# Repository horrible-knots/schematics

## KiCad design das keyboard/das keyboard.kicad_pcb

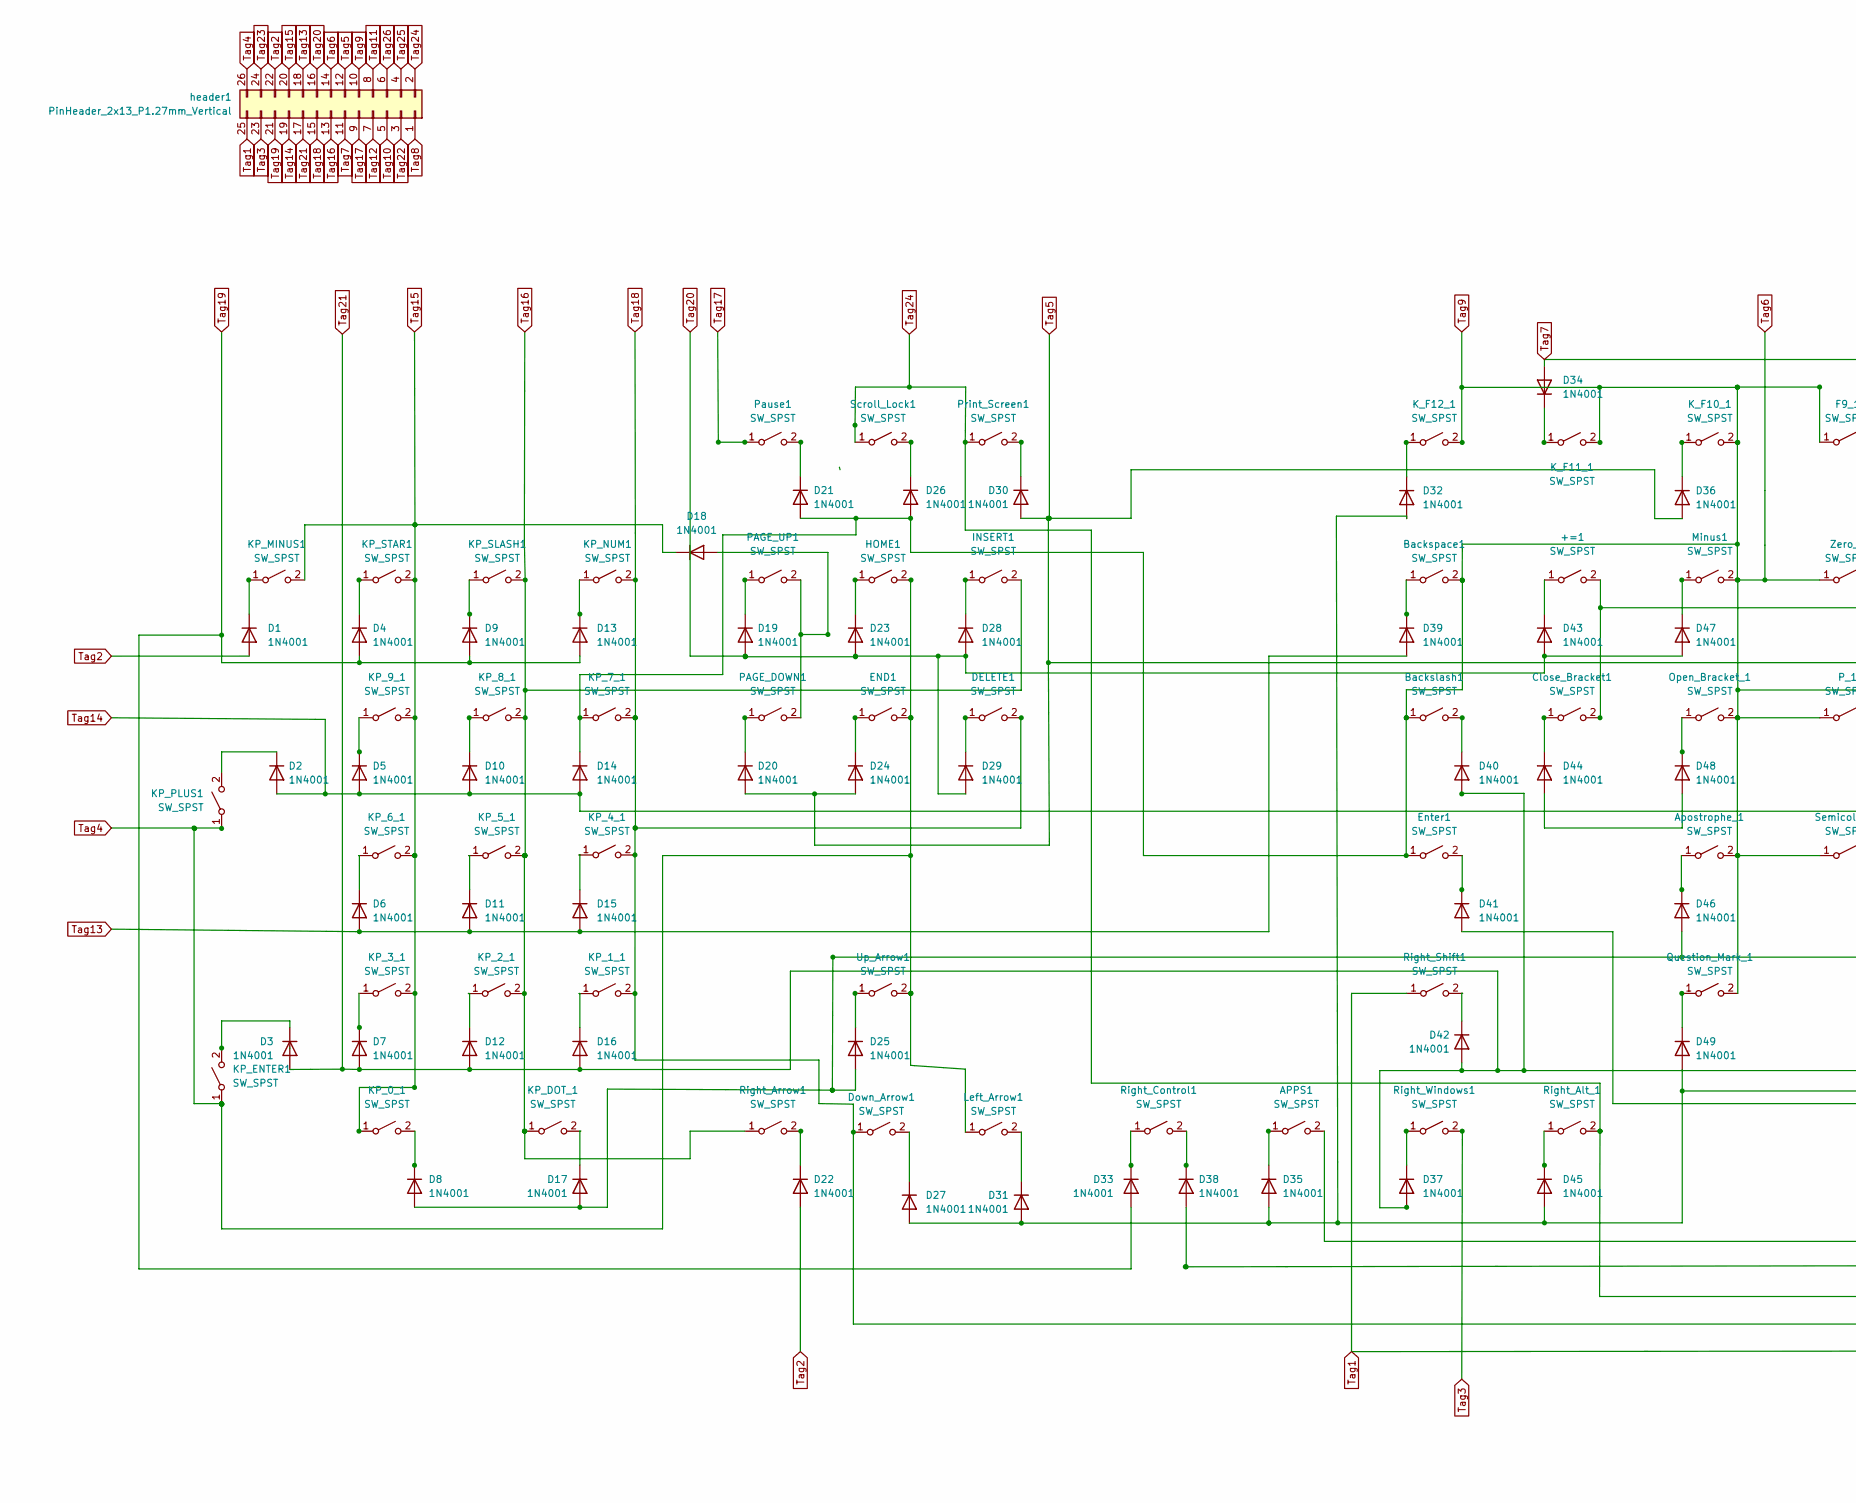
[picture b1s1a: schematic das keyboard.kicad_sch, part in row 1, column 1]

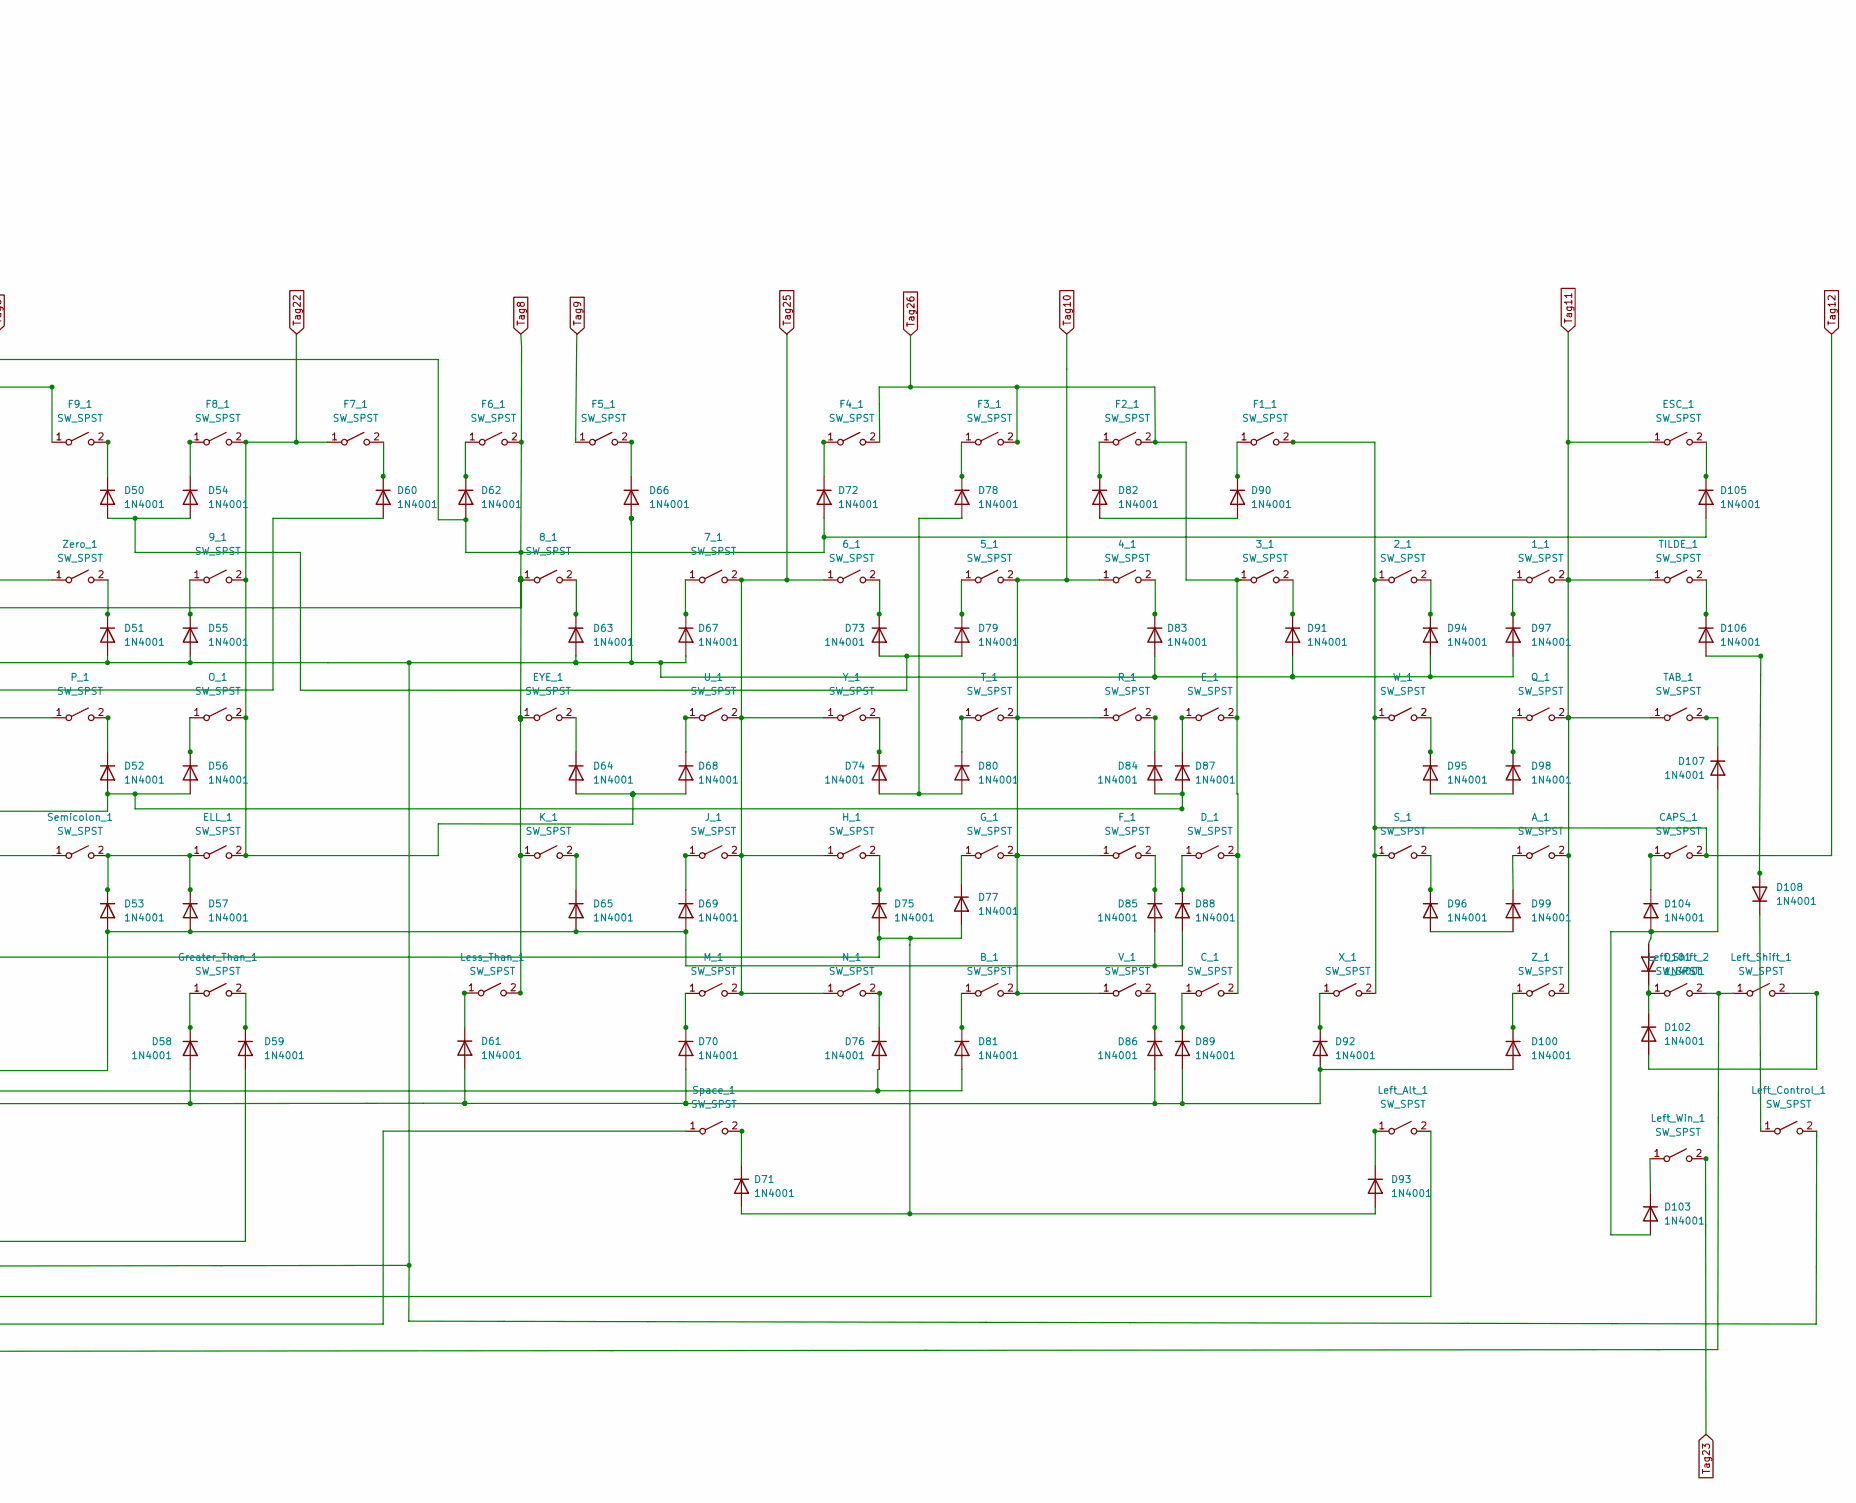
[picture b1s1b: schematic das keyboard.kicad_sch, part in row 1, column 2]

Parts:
1_1, 2_1, 3_1, 4_1, 5_1, 6_1, 7_1, 8_1, 9_1: SW_SPST; SW_Cherry_MX_1.00u_PCB
+=1: SW_SPST; SW_Cherry_MX_1.00u_PCB
APPS1: SW_SPST; SW_Cherry_MX_1.00u_PCB
A_1: SW_SPST; SW_Cherry_MX_1.00u_PCB
Apostrophe_1: SW_SPST; SW_Cherry_MX_1.00u_PCB
B_1: SW_SPST; SW_Cherry_MX_1.00u_PCB
Backslash1: SW_SPST; SW_Cherry_MX_1.50u_PCB
Backspace1: SW_SPST; SW_Cherry_MX_2.00u_PCB
CAPS_1: SW_SPST; SW_Cherry_MX_1.50u_PCB
C_1: SW_SPST; SW_Cherry_MX_1.00u_PCB
Close_Bracket1: SW_SPST; SW_Cherry_MX_1.00u_PCB
D1, D2, D3, D4, D5, D6, D7, D8, D9, D10, D11, D12, D13, D14, D15, D16, D17, D18, D19, D20, D21, D22, D23, D24, D25, D26, D27, D28, D29, D30, D31, D32, D33, D34, D35, D36, D37, D38, D39, D40, D41, D42, D43, D44, D45, D46, D47, D48, D49, D50, D51, D52, D53, D54, D55, D56, D57, D58, D59, D60, D61, D62, D63, D64, D65, D66, D67, D68, D69, D70, D71, D72, D73, D74, D75, D76, D77, D78, D79, D80, D81, D82, D83, D84, D85, D86, D87, D88, D89, D90, D91, D92, D93, D94, D95, D96, D97, D98, D99, D100, D101, D102, D103, D104, D105, D106, D107, D108: 1N4001; D_DO-41_SOD81_P10.16mm_Horizontal
DELETE1: SW_SPST; SW_Cherry_MX_1.00u_PCB
D_1: SW_SPST; SW_Cherry_MX_1.00u_PCB
Down_Arrow1: SW_SPST; SW_Cherry_MX_1.00u_PCB
ELL_1: SW_SPST; SW_Cherry_MX_1.00u_PCB
END1: SW_SPST; SW_Cherry_MX_1.00u_PCB
ESC_1: SW_SPST; SW_Cherry_MX_1.00u_PCB
EYE_1: SW_SPST; SW_Cherry_MX_1.00u_PCB
E_1: SW_SPST; SW_Cherry_MX_1.00u_PCB
Enter1: SW_SPST; SW_Cherry_MX_2.00u_PCB
F1_1, F2_1, F3_1, F4_1, F5_1, F6_1, F7_1, F8_1, F9_1: SW_SPST; SW_Cherry_MX_1.00u_PCB
F_1: SW_SPST; SW_Cherry_MX_1.00u_PCB
G_1: SW_SPST; SW_Cherry_MX_1.00u_PCB
Greater_Than_1: SW_SPST; SW_Cherry_MX_1.00u_PCB
HOME1: SW_SPST; SW_Cherry_MX_1.00u_PCB
H_1: SW_SPST; SW_Cherry_MX_1.00u_PCB
INSERT1: SW_SPST; SW_Cherry_MX_1.00u_PCB
J_1: SW_SPST; SW_Cherry_MX_1.00u_PCB
KP_0_1: SW_SPST; SW_Cherry_MX_2.00u_PCB
KP_1_1, KP_2_1, KP_3_1, KP_4_1, KP_5_1, KP_6_1, KP_7_1, KP_8_1, KP_9_1: SW_SPST; SW_Cherry_MX_1.00u_PCB
KP_DOT_1: SW_SPST; SW_Cherry_MX_1.00u_PCB
KP_ENTER1: SW_SPST; SW_Cherry_MX_2.00u_PCB
KP_MINUS1: SW_SPST; SW_Cherry_MX_1.00u_PCB
KP_NUM1: SW_SPST; SW_Cherry_MX_1.00u_PCB
KP_PLUS1: SW_SPST; SW_Cherry_MX_2.00u_PCB
KP_SLASH1: SW_SPST; SW_Cherry_MX_1.00u_PCB
KP_STAR1: SW_SPST; SW_Cherry_MX_1.00u_PCB
K_1: SW_SPST; SW_Cherry_MX_1.00u_PCB
K_F10_1, K_F11_1, K_F12_1: SW_SPST; SW_Cherry_MX_1.00u_PCB
Left_Alt_1: SW_SPST; SW_Cherry_MX_1.25u_PCB
Left_Arrow1: SW_SPST; SW_Cherry_MX_1.00u_PCB
Left_Control_1: SW_SPST; SW_Cherry_MX_1.25u_PCB
Left_Shift_1, Left_Shift_2: SW_SPST; SW_Cherry_MX_2.00u_PCB
Left_Win_1: SW_SPST; SW_Cherry_MX_1.25u_PCB
Less_Than_1: SW_SPST; SW_Cherry_MX_1.00u_PCB
M_1: SW_SPST; SW_Cherry_MX_1.00u_PCB
Minus1: SW_SPST; SW_Cherry_MX_1.00u_PCB
N_1: SW_SPST; SW_Cherry_MX_1.00u_PCB
O_1: SW_SPST; SW_Cherry_MX_1.00u_PCB
Open_Bracket_1: SW_SPST; SW_Cherry_MX_1.00u_PCB
PAGE_DOWN1: SW_SPST; SW_Cherry_MX_1.00u_PCB
PAGE_UP1: SW_SPST; SW_Cherry_MX_1.00u_PCB
P_1: SW_SPST; SW_Cherry_MX_1.00u_PCB
Pause1: SW_SPST; SW_Cherry_MX_1.00u_PCB
Print_Screen1: SW_SPST; SW_Cherry_MX_1.00u_PCB
Q_1: SW_SPST; SW_Cherry_MX_1.00u_PCB
Question_Mark_1: SW_SPST; SW_Cherry_MX_1.00u_PCB
R_1: SW_SPST; SW_Cherry_MX_1.00u_PCB
Right_Alt_1: SW_SPST; SW_Cherry_MX_1.25u_PCB
Right_Arrow1: SW_SPST; SW_Cherry_MX_1.00u_PCB
Right_Control1: SW_SPST; SW_Cherry_MX_1.00u_PCB
Right_Shift1: SW_SPST; SW_Cherry_MX_2.00u_PCB
Right_Windows1: SW_SPST; SW_Cherry_MX_1.00u_PCB
S_1: SW_SPST; SW_Cherry_MX_1.00u_PCB
Scroll_Lock1: SW_SPST; SW_Cherry_MX_1.00u_PCB
Semicolon_1: SW_SPST; SW_Cherry_MX_1.00u_PCB
Space_1: SW_SPST; SW_Cherry_MX_6.25u_PCB
TAB_1: SW_SPST; SW_Cherry_MX_1.25u_PCB
TILDE_1: SW_SPST; SW_Cherry_MX_1.00u_PCB
T_1: SW_SPST; SW_Cherry_MX_1.00u_PCB
U_1: SW_SPST; SW_Cherry_MX_1.00u_PCB
Up_Arrow1: SW_SPST; SW_Cherry_MX_1.00u_PCB
V_1: SW_SPST; SW_Cherry_MX_1.00u_PCB
W_1: SW_SPST; SW_Cherry_MX_1.00u_PCB
X_1: SW_SPST; SW_Cherry_MX_1.00u_PCB
Y_1: SW_SPST; SW_Cherry_MX_1.00u_PCB
Z_1: SW_SPST; SW_Cherry_MX_1.00u_PCB
Zero_1: SW_SPST; SW_Cherry_MX_1.00u_PCB
header1: PinHeader_2x13_P1.27mm_Vertical

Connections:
unnamed: 1_1.1 (A), D97.1 (K)
unnamed: 2_1.2 (B), D94.1 (K)
unnamed: 3_1.2 (B), D91.1 (K)
unnamed: 4_1.2 (B), D83.1 (K)
unnamed: 5_1.1 (A), D79.1 (K)
unnamed: 6_1.2 (B), D73.1 (K)
unnamed: 7_1.1 (A), D67.1 (K)
unnamed: 8_1.2 (B), D63.1 (K)
unnamed: 9_1.1 (A), D55.1 (K)
unnamed: +=1.1 (A), D43.1 (K)
unnamed: APPS1.2 (B), D59.2 (A)
unnamed: A_1.1 (A), D99.1 (K)
unnamed: Apostrophe_1.1 (A), D46.1 (K)
unnamed: B_1.1 (A), D81.1 (K)
unnamed: Backspace1.1 (A), D39.1 (K)
unnamed: CAPS_1.1 (A), D104.1 (K)
unnamed: C_1.1 (A), D89.1 (K)
unnamed: Close_Bracket1.1 (A), D44.1 (K)
unnamed: D2.1 (K), KP_PLUS1.2 (B)
unnamed: D5.1 (K), KP_9_1.1 (A)
unnamed: D6.1 (K), KP_6_1.1 (A)
unnamed: D7.1 (K), KP_3_1.1 (A)
unnamed: D8.1 (K), KP_0_1.2 (B)
unnamed: D9.1 (K), KP_SLASH1.1 (A)
unnamed: D11.1 (K), KP_5_1.1 (A)
unnamed: D12.1 (K), KP_2_1.1 (A)
unnamed: D13.1 (K), KP_NUM1.1 (A)
unnamed: D15.1 (K), KP_4_1.1 (A)
unnamed: D16.1 (K), KP_1_1.1 (A)
unnamed: D17.1 (K), KP_DOT_1.2 (B)
unnamed: D8.2 (A), D17.2 (A), D25.2 (A), D46.2 (A), D71.2 (A), D75.2 (A), D77.2 (A), D93.2 (A)
unnamed: D18.2 (A), PAGE_DOWN1.2 (B), PAGE_UP1.2 (B)
unnamed: D27.1 (K), Down_Arrow1.2 (B)
unnamed: D31.1 (K), Left_Arrow1.2 (B)
unnamed: D27.2 (A), D31.2 (A), D32.2 (A), D35.2 (A), D45.2 (A), D49.2 (A), D76.2 (A), D81.2 (A)
unnamed: D33.1 (K), Right_Control1.1 (A)
unnamed: D44.2 (A), D48.2 (A)
unnamed: D50.2 (A), D54.2 (A), D73.2 (A), D79.2 (A)
unnamed: D74.2 (A), D78.2 (A), D80.2 (A)
unnamed: D82.2 (A), D90.2 (A)
unnamed: D95.2 (A), D98.2 (A)
unnamed: D96.2 (A), D99.2 (A)
unnamed: D41.2 (A), D58.2 (A), D61.2 (A), D70.2 (A), D86.2 (A), D89.2 (A), D92.2 (A), D100.2 (A)
unnamed: D101.2 (A), D103.2 (A), D104.2 (A), D107.2 (A)
unnamed: D106.2 (A), D108.2 (A)
unnamed: D29.1 (K), DELETE1.1 (A)
unnamed: D88.1 (K), D_1.1 (A)
unnamed: D24.1 (K), END1.1 (A)
unnamed: D105.1 (K), ESC_1.2 (B)
unnamed: D64.1 (K), EYE_1.2 (B)
unnamed: D87.1 (K), E_1.1 (A)
unnamed: D41.1 (K), Enter1.2 (B)
unnamed: D90.1 (K), F1_1.1 (A)
unnamed: D82.1 (K), F2_1.1 (A)
unnamed: D78.1 (K), F3_1.1 (A)
unnamed: D72.1 (K), F4_1.1 (A)
unnamed: D66.1 (K), F5_1.2 (B)
unnamed: D62.1 (K), F6_1.1 (A)
unnamed: D60.1 (K), F7_1.2 (B)
unnamed: D54.1 (K), F8_1.1 (A)
unnamed: D50.1 (K), F9_1.2 (B)
unnamed: D85.1 (K), F_1.2 (B)
unnamed: D77.1 (K), G_1.1 (A)
unnamed: D58.1 (K), Greater_Than_1.1 (A)
unnamed: D59.1 (K), Greater_Than_1.2 (B)
unnamed: D23.1 (K), HOME1.1 (A)
unnamed: D75.1 (K), H_1.2 (B)
unnamed: D28.1 (K), INSERT1.1 (A)
unnamed: D69.1 (K), J_1.1 (A)
unnamed: D10.1 (K), KP_8_1.1 (A)
unnamed: D3.1 (K), KP_ENTER1.2 (B)
unnamed: D1.1 (K), KP_MINUS1.1 (A)
unnamed: D4.1 (K), KP_STAR1.1 (A)
unnamed: D65.1 (K), K_1.2 (B)
unnamed: D36.1 (K), K_F10_1.1 (A)
unnamed: D34.1 (K), K_F11_1.1 (A)
unnamed: D32.1 (K), K_F12_1.1 (A)
unnamed: D93.1 (K), Left_Alt_1.1 (A)
unnamed: D108.1 (K), Left_Control_1.1 (A)
unnamed: D102.2 (A), Left_Shift_1.2 (B)
unnamed: D101.1 (K), D102.1 (K), Left_Shift_2.1 (A)
unnamed: D103.1 (K), Left_Win_1.1 (A)
unnamed: D61.1 (K), Less_Than_1.1 (A)
unnamed: D70.1 (K), M_1.1 (A)
unnamed: D47.1 (K), Minus1.1 (A)
unnamed: D76.1 (K), N_1.2 (B)
unnamed: D56.1 (K), O_1.1 (A)
unnamed: D48.1 (K), Open_Bracket_1.1 (A)
unnamed: D20.1 (K), PAGE_DOWN1.1 (A)
unnamed: D19.1 (K), PAGE_UP1.1 (A)
unnamed: D52.1 (K), P_1.2 (B)
unnamed: D21.1 (K), Pause1.2 (B)
unnamed: D30.1 (K), Print_Screen1.2 (B)
unnamed: D98.1 (K), Q_1.1 (A)
unnamed: D49.1 (K), Question_Mark_1.1 (A)
unnamed: D84.1 (K), R_1.2 (B)
unnamed: D45.1 (K), Right_Alt_1.1 (A)
unnamed: D22.1 (K), Right_Arrow1.2 (B)
unnamed: D38.1 (K), Right_Control1.2 (B)
unnamed: D42.1 (K), Right_Shift1.2 (B)
unnamed: D37.1 (K), Right_Windows1.1 (A)
unnamed: D96.1 (K), S_1.2 (B)
unnamed: D26.1 (K), Scroll_Lock1.2 (B)
unnamed: D53.1 (K), D57.1 (K), ELL_1.1 (A), Semicolon_1.2 (B)
unnamed: D71.1 (K), Space_1.2 (B)
unnamed: D107.1 (K), TAB_1.2 (B)
unnamed: D106.1 (K), TILDE_1.2 (B)
unnamed: D80.1 (K), T_1.1 (A)
unnamed: D68.1 (K), U_1.1 (A)
unnamed: D25.1 (K), Up_Arrow1.1 (A)
unnamed: END1.2 (B), HOME1.2 (B), Left_Arrow1.1 (A), Up_Arrow1.2 (B)
unnamed: D86.1 (K), V_1.2 (B)
unnamed: D95.1 (K), W_1.2 (B)
unnamed: D92.1 (K), X_1.1 (A)
unnamed: D74.1 (K), Y_1.2 (B)
unnamed: D100.1 (K), Z_1.1 (A)
unnamed: D51.1 (K), Zero_1.2 (B)
Tag1: Left_Shift_1.1 (A), Left_Shift_2.2 (B), Right_Shift1.1 (A), header1.25
Tag2: D1.2 (A), D22.2 (A), header1.22
Tag3: Right_Windows1.2 (B), header1.23
Tag4: KP_ENTER1.1 (A), KP_PLUS1.1 (A), header1.26
Tag5: D20.2 (A), D24.2 (A), D30.2 (A), D36.2 (A), D38.2 (A), D51.2 (A), D55.2 (A), D63.2 (A), D66.2 (A), D67.2 (A), D83.2 (A), D91.2 (A), D94.2 (A), D97.2 (A), Left_Control_1.2 (B), header1.12
Tag6: Apostrophe_1.2 (B), Backslash1.1 (A), Backspace1.2 (B), D14.1 (K), D21.2 (A), D26.2 (A), D60.2 (A), Enter1.1 (A), F5_1.1 (A), F9_1.1 (A), KP_7_1.1 (A), K_F10_1.2 (B), K_F11_1.2 (B), Minus1.2 (B), Open_Bracket_1.2 (B), P_1.1 (A), Question_Mark_1.2 (B), Semicolon_1.1 (A), Zero_1.1 (A), header1.10, header1.14
Tag7: 8_1.1 (A), +=1.2 (B), Close_Bracket1.2 (B), D34.2 (A), D62.2 (A), D72.2 (A), D105.2 (A), F6_1.2 (B), K_1.1 (A), header1.1, header1.11
Tag10: 4_1.1 (A), 5_1.2 (B), B_1.2 (B), F_1.1 (A), G_1.2 (B), R_1.1 (A), T_1.2 (B), V_1.1 (A), header1.5
Tag11: 1_1.2 (B), A_1.2 (B), ESC_1.1 (A), Q_1.2 (B), TAB_1.1 (A), TILDE_1.1 (A), Z_1.2 (B), header1.8
Tag12: 2_1.1 (A), CAPS_1.2 (B), F1_1.2 (B), S_1.1 (A), W_1.1 (A), X_1.2 (B), header1.7
Tag13: D6.2 (A), D11.2 (A), D15.2 (A), D39.2 (A), header1.18
Tag14: D2.2 (A), D5.2 (A), D10.2 (A), D14.2 (A), D52.2 (A), D56.2 (A), D84.2 (A), D87.2 (A), header1.19
Tag15: D18.1 (K), KP_0_1.1 (A), KP_3_1.2 (B), KP_6_1.2 (B), KP_9_1.2 (B), KP_MINUS1.2 (B), KP_STAR1.2 (B), header1.20
Tag16: INSERT1.2 (B), KP_2_1.2 (B), KP_5_1.2 (B), KP_8_1.2 (B), KP_DOT_1.1 (A), KP_SLASH1.2 (B), Right_Arrow1.1 (A), header1.13
Tag17: Pause1.1 (A), header1.9
Tag18: DELETE1.2 (B), Down_Arrow1.1 (A), KP_1_1.2 (B), KP_7_1.2 (B), KP_NUM1.2 (B), Space_1.1 (A), header1.15
Tag19: D4.2 (A), D9.2 (A), D13.2 (A), D33.2 (A), header1.21
Tag20: D19.2 (A), D23.2 (A), D28.2 (A), D29.2 (A), D43.2 (A), D47.2 (A), header1.16
Tag21: D3.2 (A), D7.2 (A), D12.2 (A), D16.2 (A), D37.2 (A), D40.2 (A), D42.2 (A), D53.2 (A), D57.2 (A), D65.2 (A), D69.2 (A), D85.2 (A), D88.2 (A), header1.17
Tag22: 9_1.2 (B), D64.2 (A), D68.2 (A), ELL_1.2 (B), F7_1.1 (A), F8_1.2 (B), O_1.2 (B), header1.3
Tag23: Left_Win_1.2 (B), header1.24
Tag24: Left_Alt_1.2 (B), Print_Screen1.1 (A), Right_Alt_1.2 (B), Scroll_Lock1.1 (A), header1.2
Tag25: 6_1.1 (A), 7_1.2 (B), H_1.1 (A), J_1.2 (B), M_1.2 (B), N_1.1 (A), U_1.2 (B), Y_1.1 (A), header1.4
Tag26: 3_1.1 (A), C_1.2 (B), D_1.2 (B), E_1.2 (B), F2_1.2 (B), F3_1.2 (B), F4_1.2 (B), header1.6

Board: 2 copper layers, 214 parts (214 on the bottom side), 141 nets, no tracks yet.

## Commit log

2022-08-28 updates to the pcb
2022-08-28 add pcb image
